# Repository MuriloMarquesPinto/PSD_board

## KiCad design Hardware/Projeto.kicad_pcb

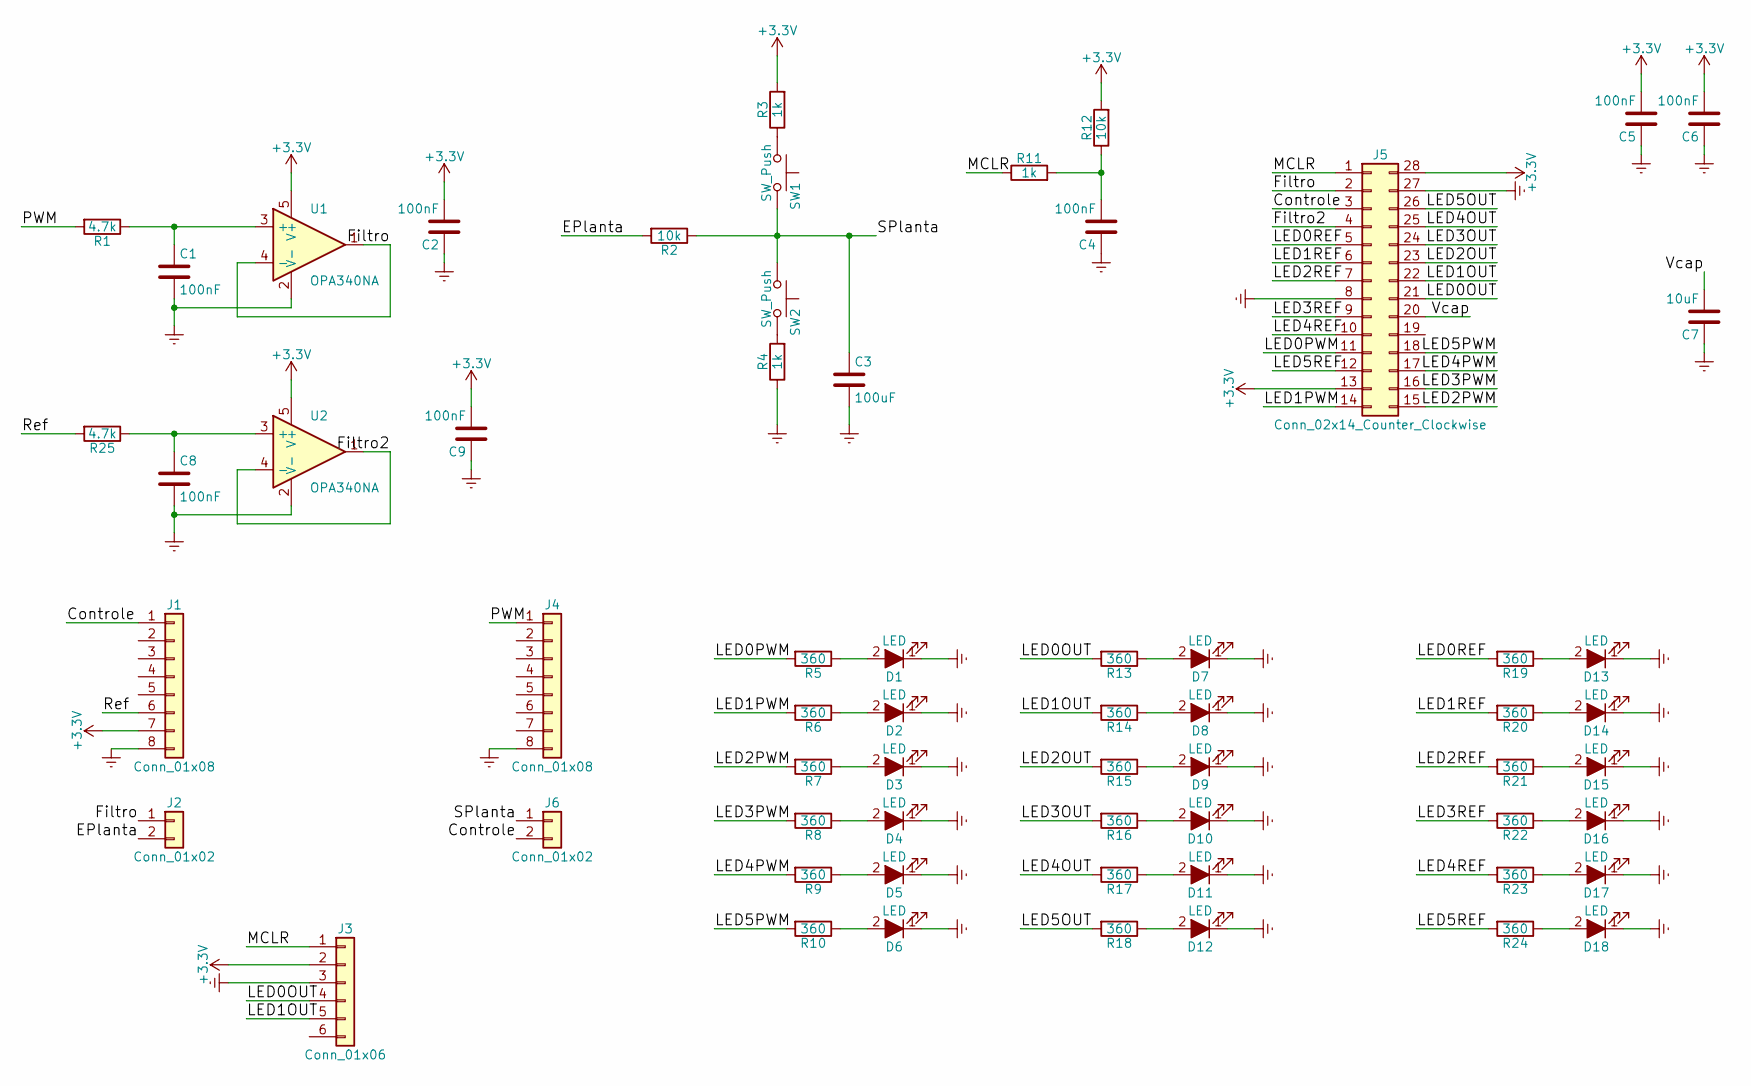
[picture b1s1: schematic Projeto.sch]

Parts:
C1, C2, C4, C5, C6, C8, C9: 100nF; C_0805
C3: 100uF; CP_Elec_5x5.3
C7: 10uF; C_0805
D1, D2, D3, D4, D5, D6, D7, D8, D9, D10, D11, D12, D13, D14, D15, D16, D17, D18: LED; LED_0805
J1, J4: Conn_01x08; Pin_Header_Straight_1x08_Pitch2.54mm
J2, J6: Conn_01x02; Pin_Header_Straight_1x02_Pitch2.54mm
J3: Conn_01x06; Pin_Header_Straight_1x06_Pitch2.54mm
J5: Conn_02x14_Counter_Clockwise; SSOP-28_5.3x10.2mm_Pitch0.65mm
R1, R25: 4.7k; R_0805
R2: 10k; R_Axial_DIN0614_L14.3mm_D5.7mm_P15.24mm_Horizontal
R3, R4, R11: 1k; R_0805
R5, R6, R7, R8, R9, R10, R13, R14, R15, R16, R17, R18, R19, R20, R21, R22, R23, R24: 360; R_0805
R12: 10k; R_0805
SW1, SW2: SW_Push; SW_PUSH_6mm
U1, U2: OPA340NA; SOT-23-5_HandSoldering

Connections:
+3V3: C2.2, C5.2, C6.2, C9.2, J1.7, J3.2, J5.13, J5.28, R3.2, R12.2, U1.5 (V+), U2.5 (V+)
/Controle: J1.1, J5.3, J6.2
/EPlanta: J2.2, R2.2
/Filtro: J2.1, J5.2, U1.1, U1.4 (-)
/Filtro2: J5.4, U2.1, U2.4 (-)
/LED0OUT: J3.4, J5.21, R13.2
/LED0PWM: J5.11, R5.2
/LED0REF: J5.5, R19.2
/LED1OUT: J3.5, J5.22, R14.2
/LED1PWM: J5.14, R6.2
/LED1REF: J5.6, R20.2
/LED2OUT: J5.23, R15.2
/LED2PWM: J5.15, R7.2
/LED2REF: J5.7, R21.2
/LED3OUT: J5.24, R16.2
/LED3PWM: J5.16, R8.2
/LED3REF: J5.9, R22.2
/LED4OUT: J5.25, R17.2
/LED4PWM: J5.17, R9.2
/LED4REF: J5.10, R23.2
/LED5OUT: J5.26, R18.2
/LED5PWM: J5.18, R10.2
/LED5REF: J5.12, R24.2
/MCLR: J3.1, J5.1, R11.1
/PWM: J4.1, R1.2
/Ref: J1.6, R25.2
/SPlanta: C3.1, J6.1, R2.1, SW1.2, SW2.1
/Vcap: C7.2, J5.20
Earth: C1.2, C2.1, C3.2, C4.1, C5.1, C6.1, C7.1, C8.2, C9.1, D1.1 (K), D2.1 (K), D3.1 (K), D4.1 (K), D5.1 (K), D6.1 (K), D7.1 (K), D8.1 (K), D9.1 (K), D10.1 (K), D11.1 (K), D12.1 (K), D13.1 (K), D14.1 (K), D15.1 (K), D16.1 (K), D17.1 (K), D18.1 (K), J1.8, J3.3, J4.8, J5.8, J5.27, R4.1, U1.2 (V-), U2.2 (V-)
unnamed: C1.1, R1.1, U1.3 (+)
unnamed: C4.2, R11.2, R12.1
unnamed: C8.1, R25.1, U2.3 (+)
unnamed: D1.2 (A), R5.1
unnamed: D2.2 (A), R6.1
unnamed: D3.2 (A), R7.1
unnamed: D4.2 (A), R8.1
unnamed: D5.2 (A), R9.1
unnamed: D6.2 (A), R10.1
unnamed: D7.2 (A), R13.1
unnamed: D8.2 (A), R14.1
unnamed: D9.2 (A), R15.1
unnamed: D10.2 (A), R16.1
unnamed: D11.2 (A), R17.1
unnamed: D12.2 (A), R18.1
unnamed: D13.2 (A), R19.1
unnamed: D14.2 (A), R20.1
unnamed: D15.2 (A), R21.1
unnamed: D16.2 (A), R22.1
unnamed: D17.2 (A), R23.1
unnamed: D18.2 (A), R24.1
unnamed: R3.1, SW1.1
unnamed: R4.2, SW2.2

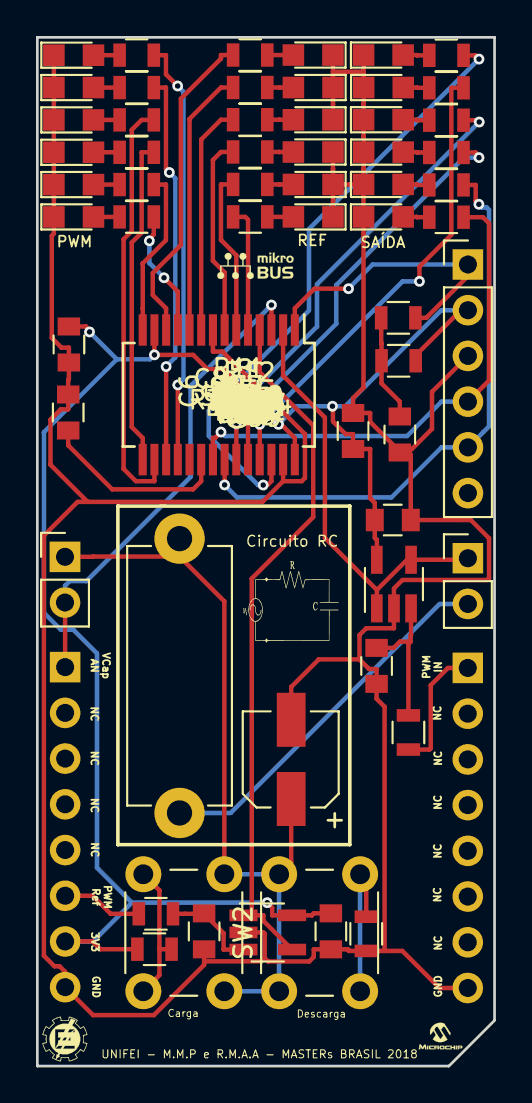
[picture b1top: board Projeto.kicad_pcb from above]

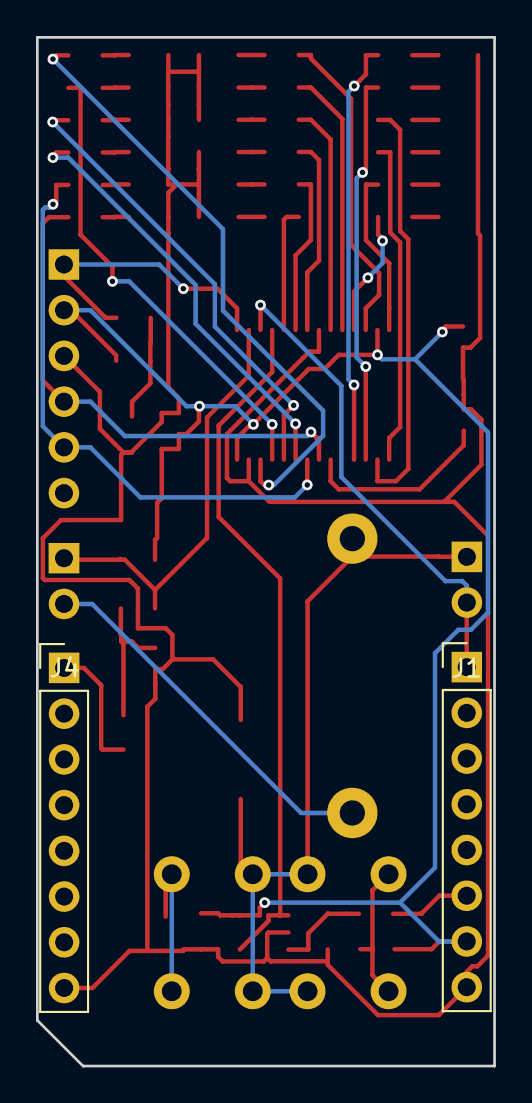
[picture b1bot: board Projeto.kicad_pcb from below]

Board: 2 copper layers, 25.4 x 57.1 mm, 63 parts (2 on the bottom side), 52 nets.

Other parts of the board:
G**1: LOGO; Circuito

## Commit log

2018-10-29 1st version
    Inital data for the plant signaldisplayboard. There is the code using freertos and the hardware project using kicad.
